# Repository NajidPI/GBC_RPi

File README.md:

# GBC_RPi
This repository includes all files required to build a functioning Gameboy Colour by retrofitting the shell with a Raspberry Pi

folders:

install - To start designing from scratch. These are the necessary versions for running KiCAD with Autorouter

GBC_motherboard - Files for a PCB design made in KiCAD and generated gerber files for printing

gbc -  holds all games loaded on the raspberry pi

Game_Boy_Zero - File to program Teensy board for gaming controls

Future works:
Merge all breakout boards onto motherboard

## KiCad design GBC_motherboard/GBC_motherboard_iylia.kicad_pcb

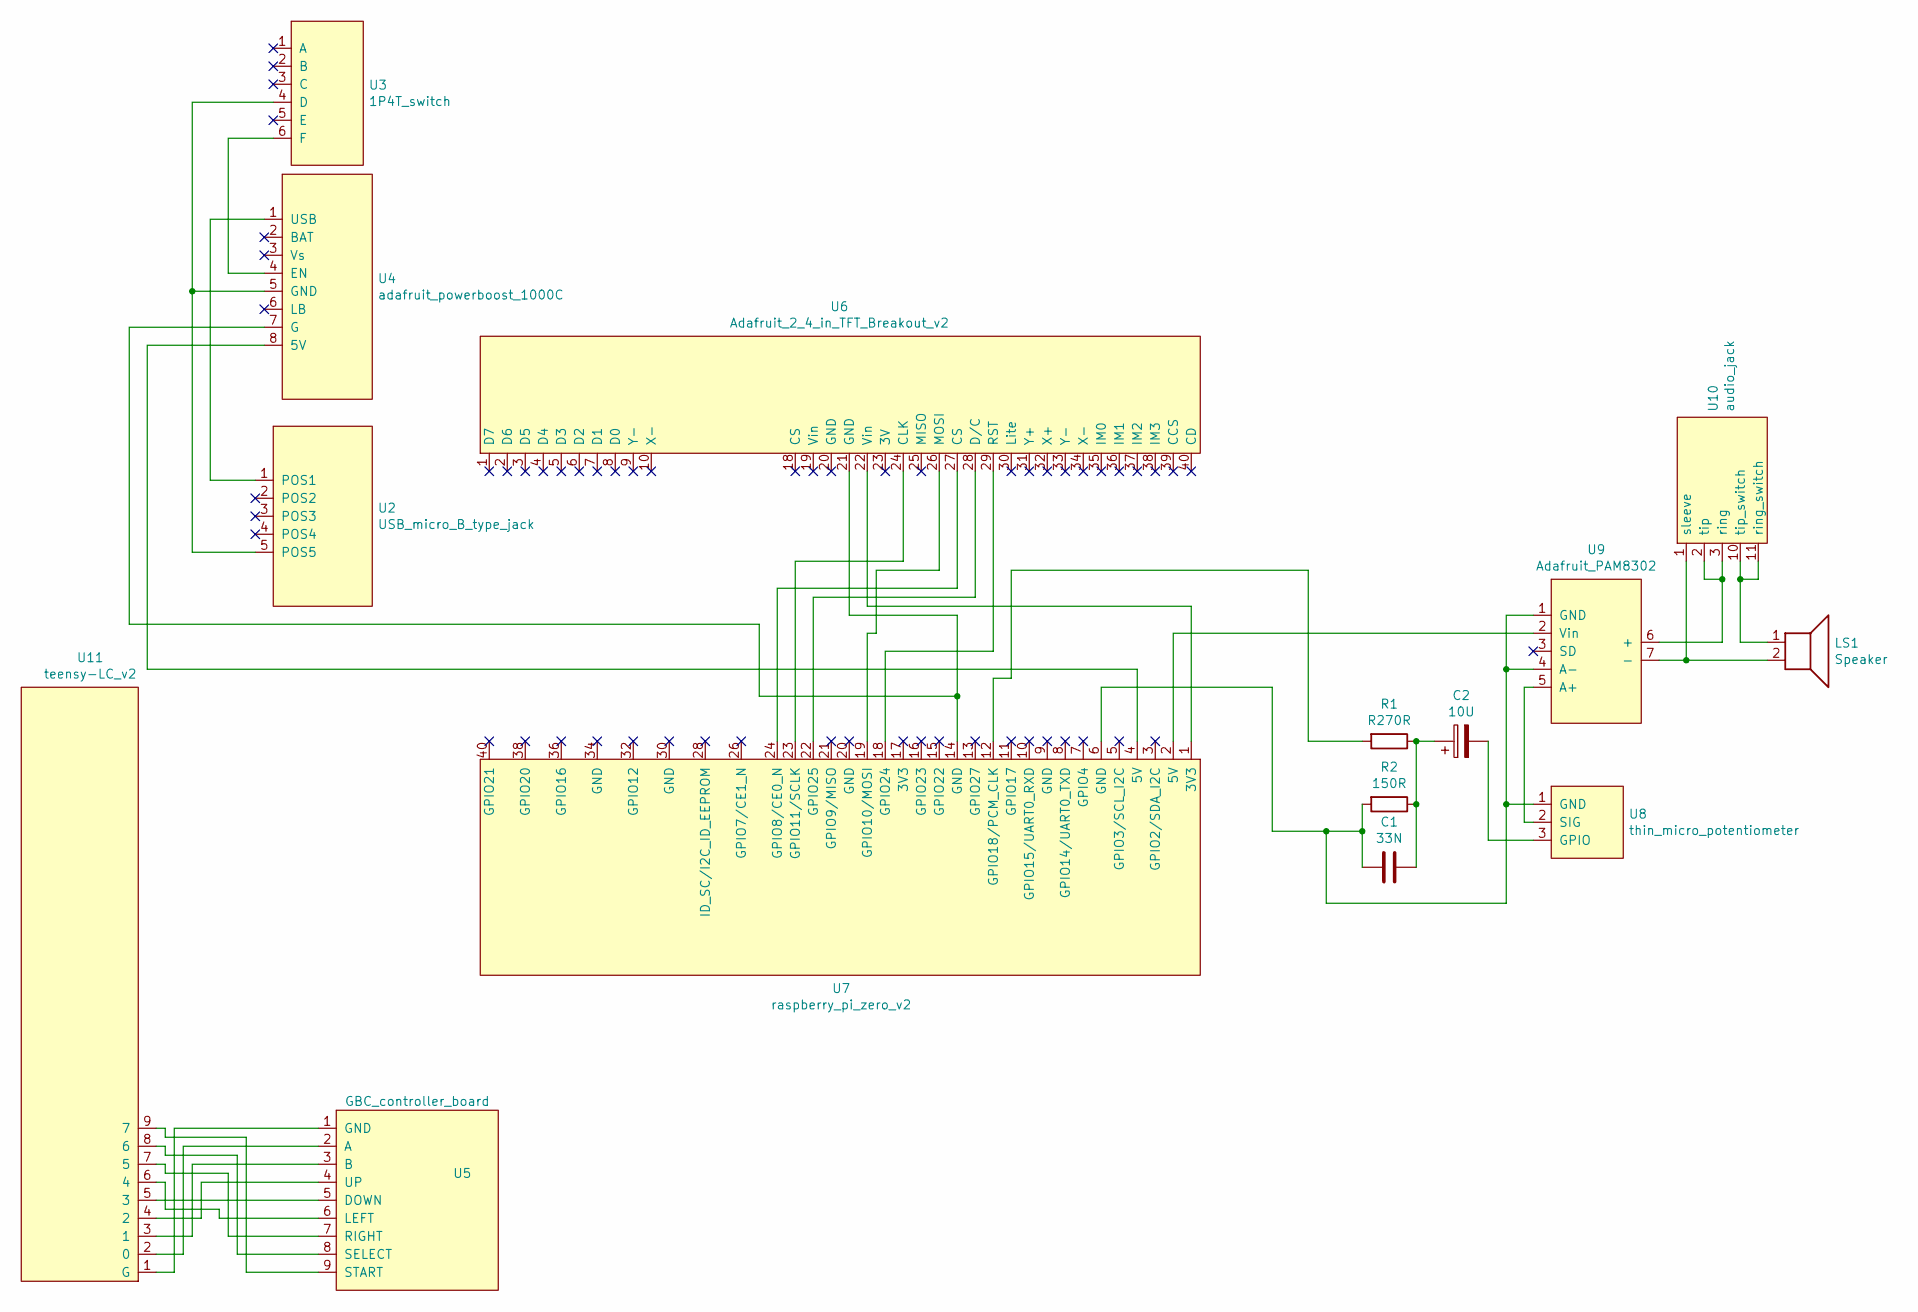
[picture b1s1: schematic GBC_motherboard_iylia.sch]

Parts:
C1: 33N; C_1206_3216Metric_Pad1.33x1.80mm_HandSolder
C2: 10U; C_1206_3216Metric_Pad1.33x1.80mm_HandSolder
LS1: Speaker; PinHeader_1x02_P2.54mm_Vertical
R1: R270R; R_1206_3216Metric_Pad1.30x1.75mm_HandSolder
R2: 150R; R_1206_3216Metric_Pad1.30x1.75mm_HandSolder
U2: USB_micro_B_type_jack
U3: 1P4T_switch
U4: adafruit_powerboost_1000C; adafruit_powerboost_1000c
U5: GBC_controller_board
U6: Adafruit_2_4_in_TFT_Breakout_v2
U7: raspberry_pi_zero_v2
U8: thin_micro_potentiometer
U9: Adafruit_PAM8302
U10: audio_jack
U11: teensy-LC_v2

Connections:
unnamed: C1.1, C2.1, R1.1, R2.1
unnamed: C1.2, R2.2, U7.6 (GND), U8.1 (GND), U9.1 (GND), U9.4 (A-)
unnamed: C2.2, U8.3 (GPIO)
unnamed: LS1.1, U10.10 (tip_switch), U10.11 (ring_switch)
unnamed: LS1.2, U9.7 (-), U10.1 (sleeve)
unnamed: R1.2, U7.12 (GPIO18/PCM_CLK)
unnamed: U2.1 (POS1), U4.1 (USB)
unnamed: U2.5 (POS5), U3.4 (D), U4.5 (GND)
unnamed: U3.6 (F), U4.4 (EN)
unnamed: U4.7 (G), U6.21 (GND), U7.14 (GND)
unnamed: U4.8 (5V), U7.4 (5V)
unnamed: U6.22 (Vin), U7.1 (3V3)
unnamed: U6.24 (CLK), U7.23 (GPIO11/SCLK)
unnamed: U6.26 (MOSI), U7.19 (GPIO10/MOSI)
unnamed: U6.27 (CS), U7.24 (GPIO8/CE0_N)
unnamed: U6.28 (D/C), U7.22 (GPIO25)
unnamed: U6.29 (RST), U7.18 (GPIO24)
unnamed: U7.2 (5V), U9.2 (Vin)
unnamed: U8.2 (SIG), U9.5 (A+)
unnamed: U9.6 (+), U10.2 (tip), U10.3 (ring)
unnamed: U5.1 (GND), U11.1 (G)
unnamed: U5.2 (A), U11.2 (0)
unnamed: U5.3 (B), U11.3 (1)
unnamed: U5.4 (UP), U11.4 (2)
unnamed: U5.5 (DOWN), U11.5 (3)
unnamed: U5.6 (LEFT), U11.6 (4)
unnamed: U5.7 (RIGHT), U11.7 (5)
unnamed: U5.8 (SELECT), U11.8 (6)
unnamed: U5.9 (START), U11.9 (7)

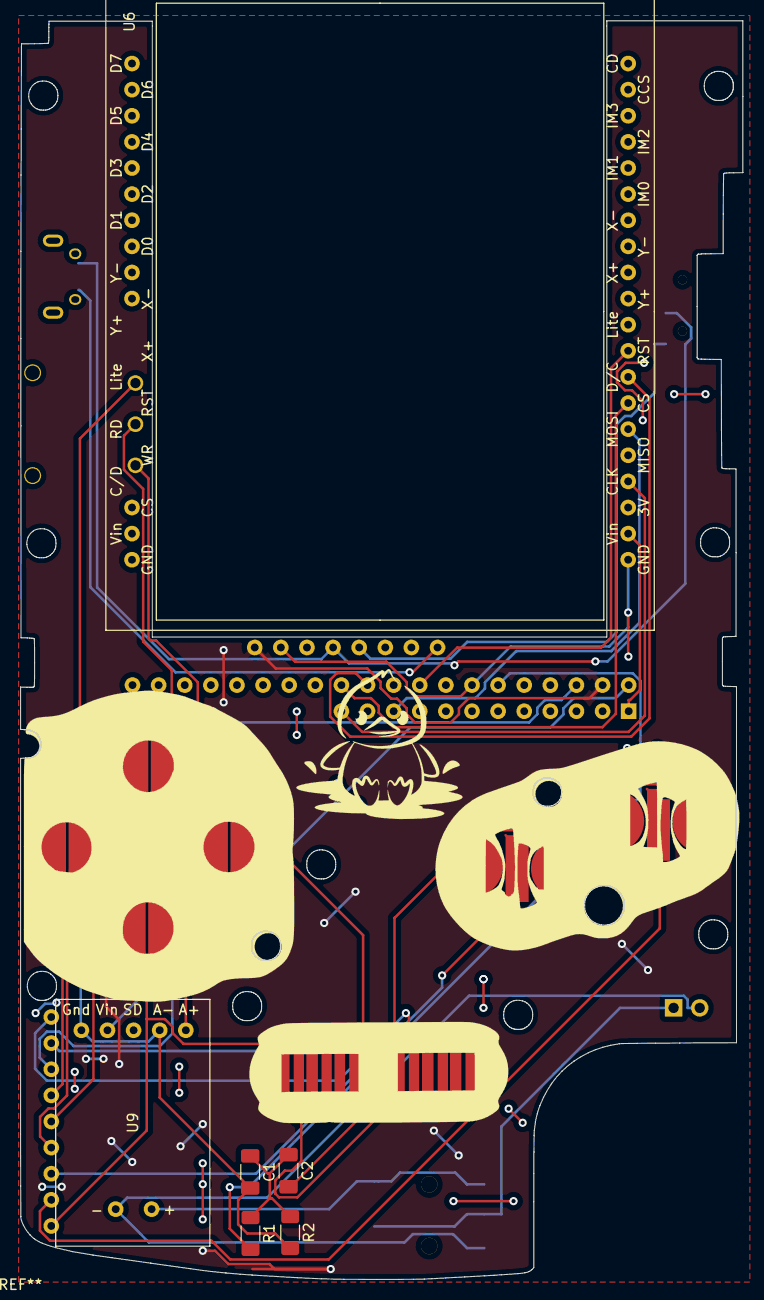
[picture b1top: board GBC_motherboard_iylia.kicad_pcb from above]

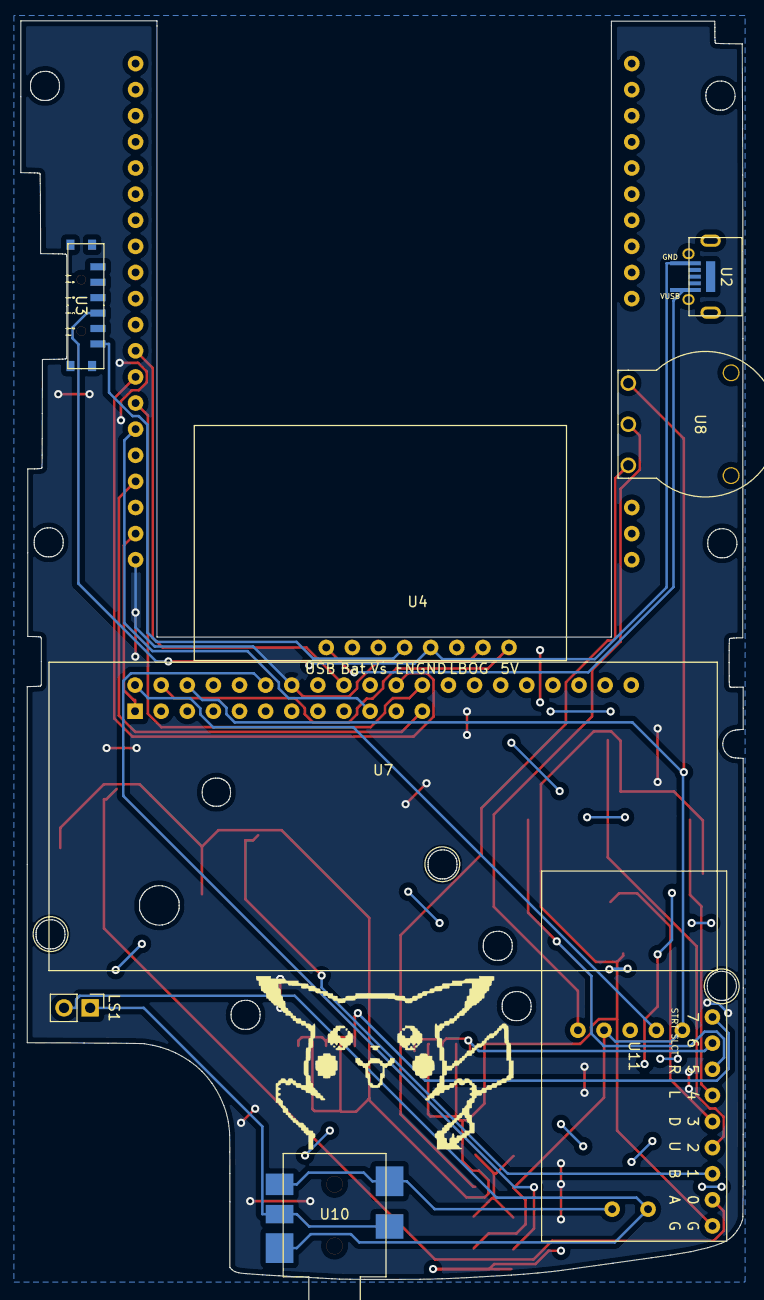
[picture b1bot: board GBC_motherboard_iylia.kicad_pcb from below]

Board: 2 copper layers, 70.3 x 122.4 mm, 17 parts (9 on the bottom side), 29 nets.

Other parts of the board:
G1: LOGO; cute-duck
G2: LOGO; pikachu

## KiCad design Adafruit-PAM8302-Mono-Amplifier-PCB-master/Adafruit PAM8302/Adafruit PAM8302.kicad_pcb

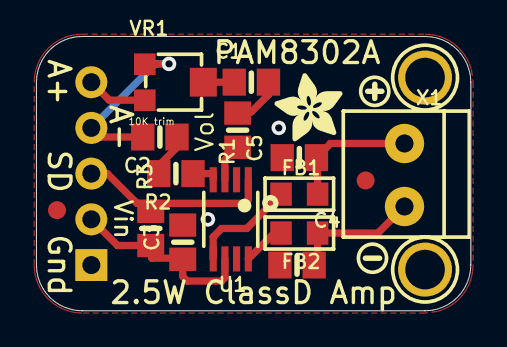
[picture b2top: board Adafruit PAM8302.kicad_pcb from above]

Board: 2 copper layers, 24.1 x 15.2 mm, 22 parts (0 on the bottom side), 14 nets.

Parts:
C1, C2: 1uF; 0805-NO
C3: 10uF; 0805-NO
C4, C5: 220pF; 0805-NO
FB1, FB2: Ferrite; _0805
FID1, FID2: FIDUCIAL; FIDUCIAL_1MM
JP1: HEADER-1X570MIL; 1X05_ROUND_70
R1, R2: 100; 0805-NO
R3: 10K; 0805-NO
U1: PAM8302AASCR; MSOP8_0.65MM
U$3: SYMBOL_PLUS
U$4: SYMBOL_MINUS
U$5: ADAFRUIT_3.5MM
U$6: PCBFEAT-REV-040
U$10, U$11: MOUNTINGHOLE2.0; MOUNTINGHOLE_2.0_PLATED
VR1: 10K trim; TRIMPOT_BOURNS_3303W
X1: TERMBLOCK_1X2; TERMBLOCK_1X2-3.5MM

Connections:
/AIN+: JP1.5, VR1.3
/AIN-: C2.2, JP1.4, VR1.1
/SD: JP1.3, R3.2, U1.1
/VO+: C5.1, FB1.2, X1.1
/VO-: C4.1, FB2.2, X1.2
GND: C3.2, C4.2, C5.2, JP1.1, U1.7
unnamed: C1.1, R1.1
unnamed: C1.2, VR1.2
unnamed: C2.1, R2.1
unnamed: FB1.1, U1.5
unnamed: FB2.1, U1.8
unnamed: R1.2, U1.3
unnamed: R2.2, U1.4
VCC: C3.1, JP1.2, R3.1, U1.6

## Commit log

2022-10-21 Dump of completed project
